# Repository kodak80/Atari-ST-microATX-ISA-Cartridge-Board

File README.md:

# Atari ST microATX ISA Cartridge Board

ISA board to allow the original Atari ST cartridge socket on a card. It brings
the ST cartridge port out to an ISA (16-bit) card outline and an internal
40-pin IDC header, so the cartridge bus can be used inside a microATX case
build. Board silkscreen: *Atari ST ATX Cartridge Port ISA Adapter v1.3 —
kodak80 (2022)*.

## Board

- Two-layer PCB in an ISA 16-bit card outline (`ST1`)
- Atari ST cartridge port connection (`U$1`) with ROM3/ROM4 select lines
- Internal 40-pin IDC header (`J1`) carrying the cartridge bus
- DIP-16 socket (`J2`) for a Dallas-style RTC ("FMC-II RTC"), with crystal
  (`Y1`) and CR1220 coin-cell holder (`BT1`)
- Jumper option on the board (`JP`)

## Files

| File | Contents |
|------|----------|
| `Cart Adapter RTC 40 pin Header SMD CR1220.kicad_pro` | KiCad project |
| `Cart Adapter RTC 40 pin Header SMD CR1220.kicad_sch` | Schematic |
| `Cart Adapter RTC 40 pin Header SMD CR1220.kicad_pcb` | PCB layout |
| `IDC-Header_2x20_P2.54mm_Vertical_kodak80.kicad_mod` | Custom 2×20 IDC header footprint |
| `empty.kicad_wks` | Drawing sheet |

Created in KiCad 6; opens in later versions (they will offer to upgrade the
file format on save). The schematic was originally imported from Eagle, so
several symbols live in the embedded `Cart Adapter-eagle-import` library.

## Revision

v1.3

## TheHulk ISA card (branch `thehulk-isa`)

[`thehulk-isa/`](thehulk-isa/) merges RetroLoft's [TheHulk](https://github.com/RetroLoft/thehulk)
network/SD storage cartridge onto this card: schematic done, PCB is this v1.3 board with the socket
and RTC removed and TheHulk's parts added, ready to be placed. KiCad 9, GPL-3.0. See
[`thehulk-isa/ROUTING.md`](thehulk-isa/ROUTING.md).

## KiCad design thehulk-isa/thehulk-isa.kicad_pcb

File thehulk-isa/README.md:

# TheHulk ISA card

[TheHulk](https://github.com/RetroLoft/thehulk) (RetroLoft's network and SD card storage cartridge for
the Atari ST, ESP32-S3 + iCE40UP5K) moved onto the Atari ST mATX ISA cartridge board in the parent
folder. The cartridge bus reaches the card through the ISA edge (same pinout as the v1.3 board) or
the internal 40-pin header J1. The /ROM3 and /ROM4 pads are kept for the flying wires from the
motherboard.

KiCad 9 project, based on TheHulk `hardware/prod-v2` (commit `c8f1c73`).

## What changed from TheHulk prod-v2

- **Cartridge edge removed.** The 40-pin cartridge connector `CON1` is now `J1`, a 2×20 IDC header
  (`isa_card:IDC-Header_2x20_P2.54mm_Vertical_kodak80`). Its pins are numbered exactly like the cartridge
  port, so nothing else in TheHulk's circuit changed.
- **ISA edge added** (`ST1`, `isa_card:ISA_16bit_Edge` / `isa_card:IBM16BIT`) on the same nets as
  v1.3: D0–D15, A1–A15, /UDS, /LDS, +5V, GND. The ISA pins v1.3 had but the cartridge port doesn't
  (A16–A19, RDY2, VRES, MEMRD/MEMWR, ±12V) are marked no-connect.
- **/ROM3 and /ROM4 wire pads** (`ROM3`, `ROM4`), as on v1.3.
- **FMC-II RTC socket and the passthrough cartridge socket are gone.**
- Everything else is TheHulk prod-v2 unchanged: same parts, same nets, same FPGA and ESP32 pins, so
  TheHulk's gateware and firmware should run as they are.

## PCB

Fresh start from the v1.3 board (`Cart Adapter RTC 40 pin Header SMD CR1220.kicad_pcb`):

- **Kept exactly as v1.3:** card outline, ISA edge (ST1), J1 and the /ROM3, /ROM4 pads in their
  v1.3 positions, and your v1.3 routing between the ISA edge, J1 and the /ROM pads.
- **Removed:** the cartridge socket, the FMC-II RTC (Dallas socket, crystal, CR1220 holder), their
  silkscreen labels, and the v1.3 tracks that only went to them.
- **Added, not placed:** all 74 of TheHulk's parts (everything except its cartridge edge), with
  their nets, sitting below the card in TheHulk's own arrangement under the label
  "TheHulk parts - to be placed". No tracks.
- Net class: TheHulk's (0.2 mm tracks, 0.6/0.3 mm vias) with the clearance set to 0.1524 mm (6 mil),
  the clearance your v1.3 routing was laid out to. TheHulk's own layout also meets it.

## License

GPL-3.0 (see `LICENSE`), as TheHulk. TheHulk is by RetroLoft; GEMDRIVE is based on the
SidecarTridge Multi-device project by Diego Parrilla Santamaría (GOODDATA LABS SL).

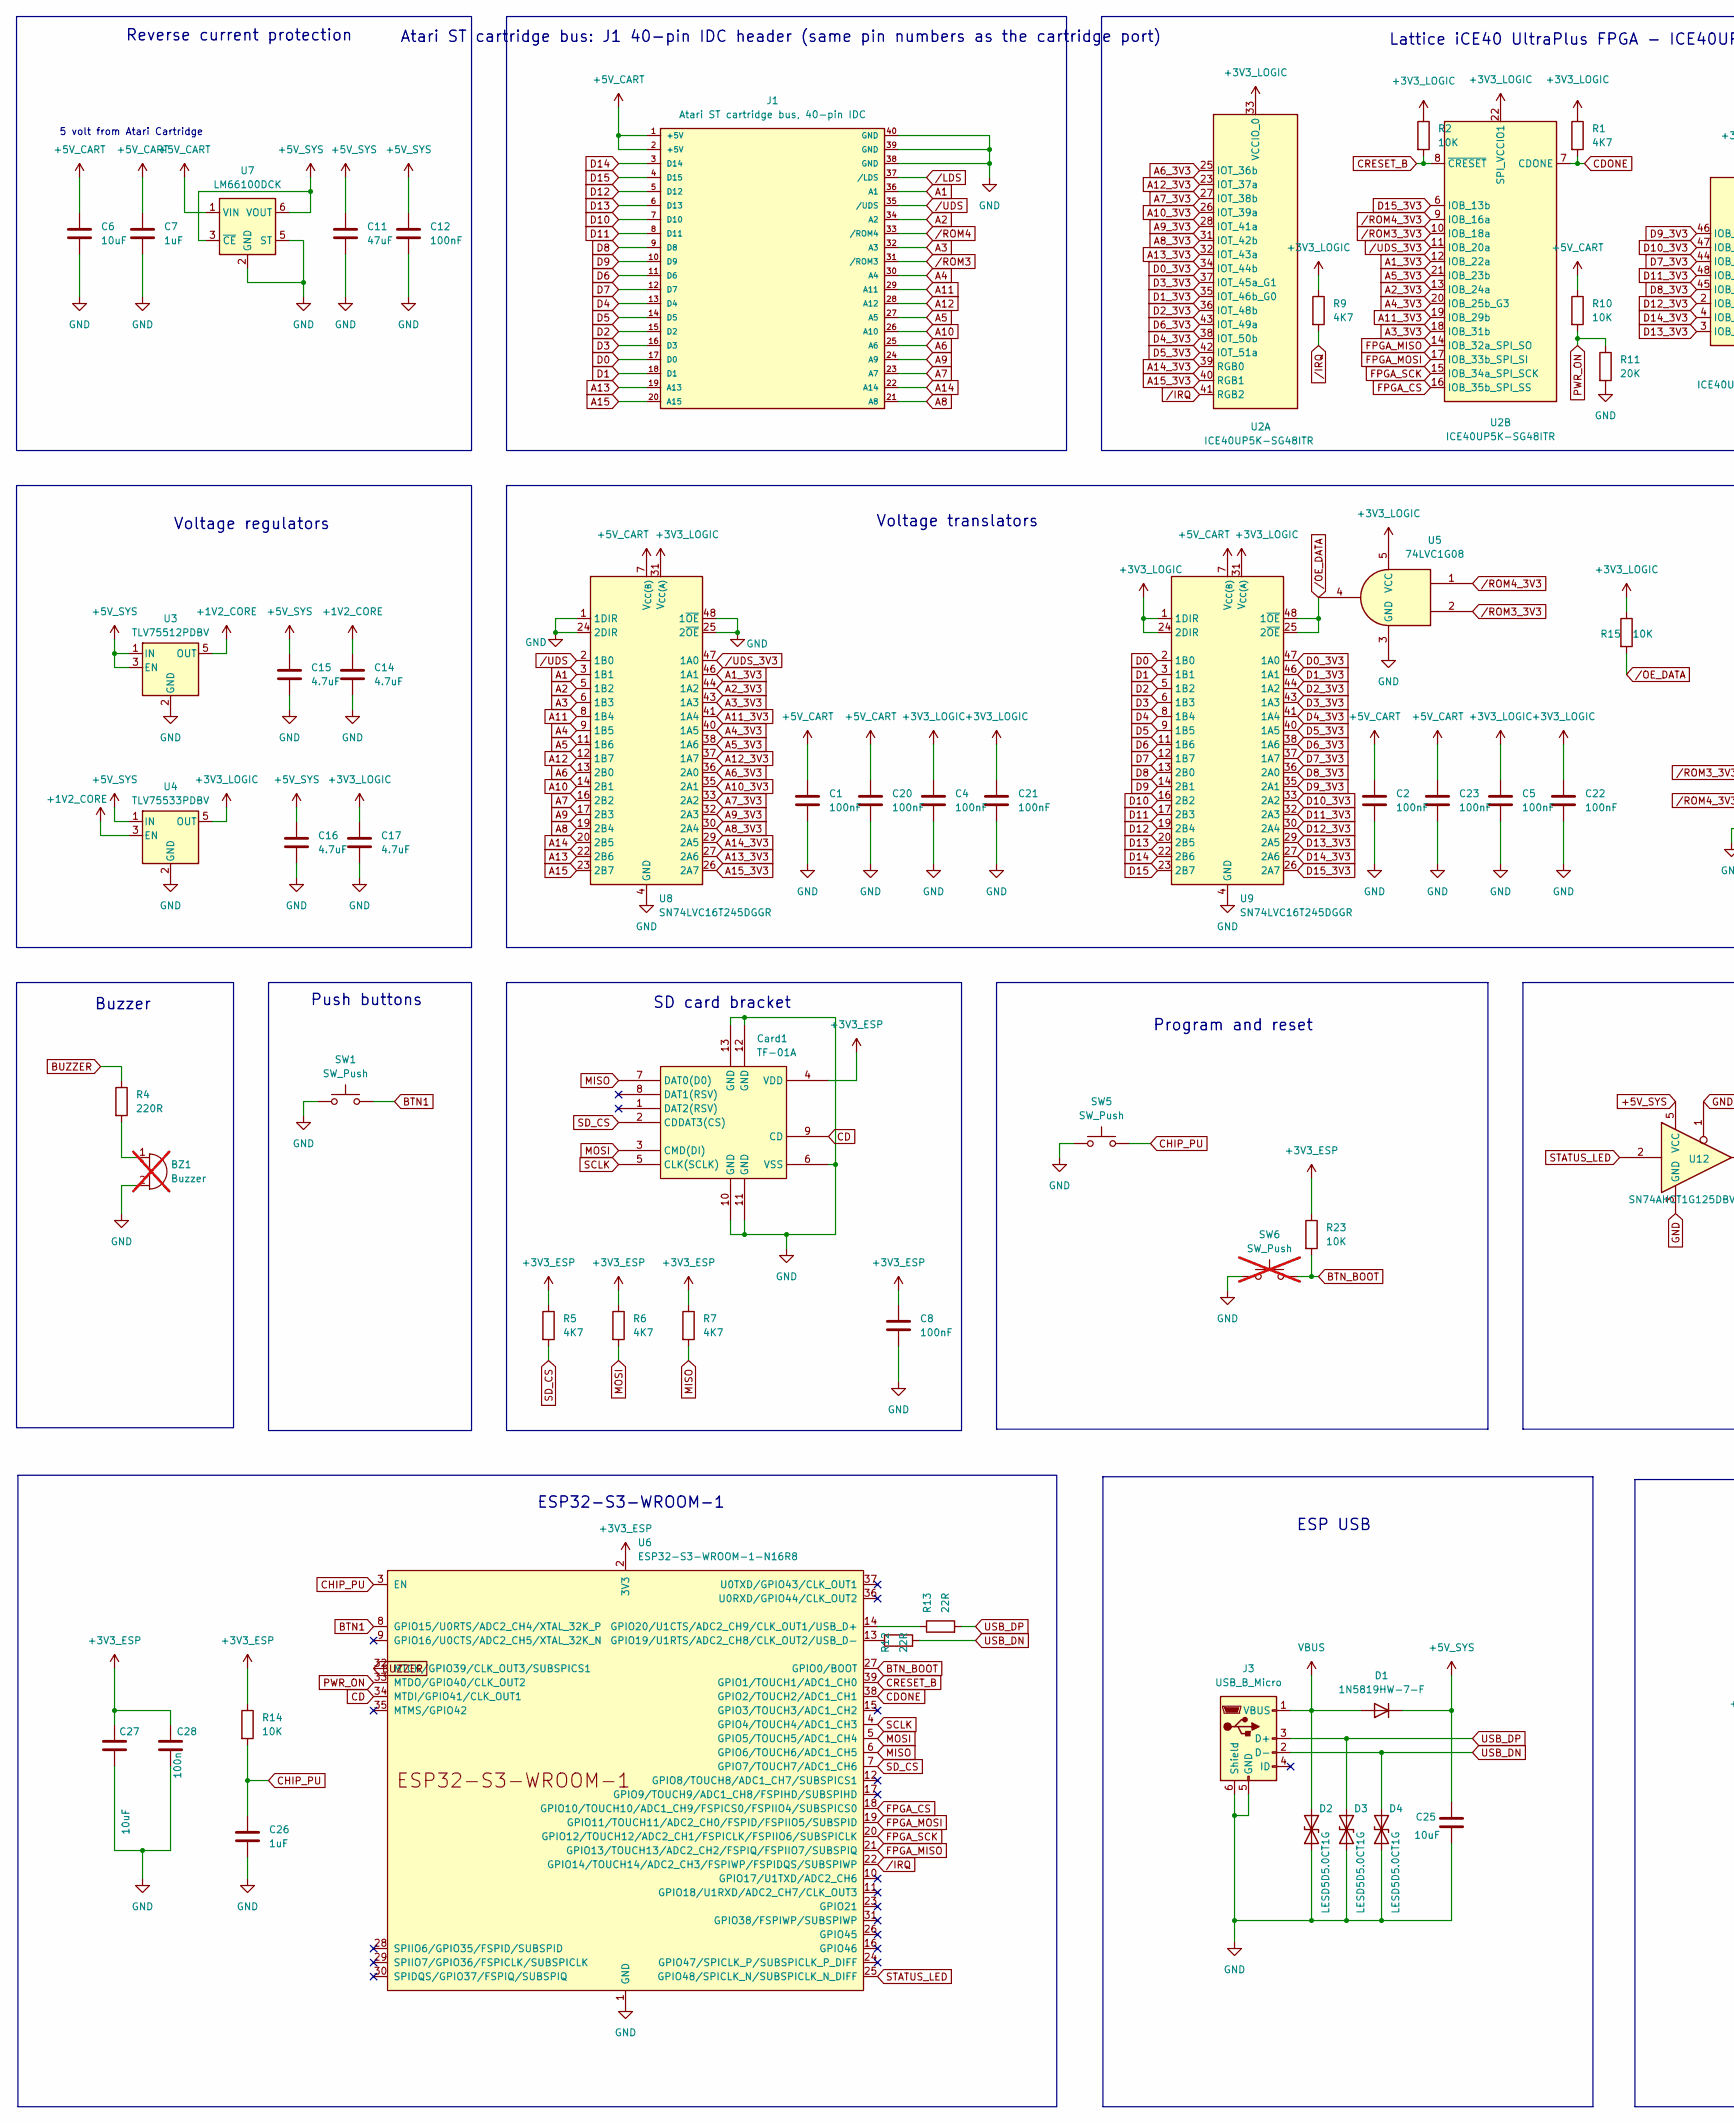
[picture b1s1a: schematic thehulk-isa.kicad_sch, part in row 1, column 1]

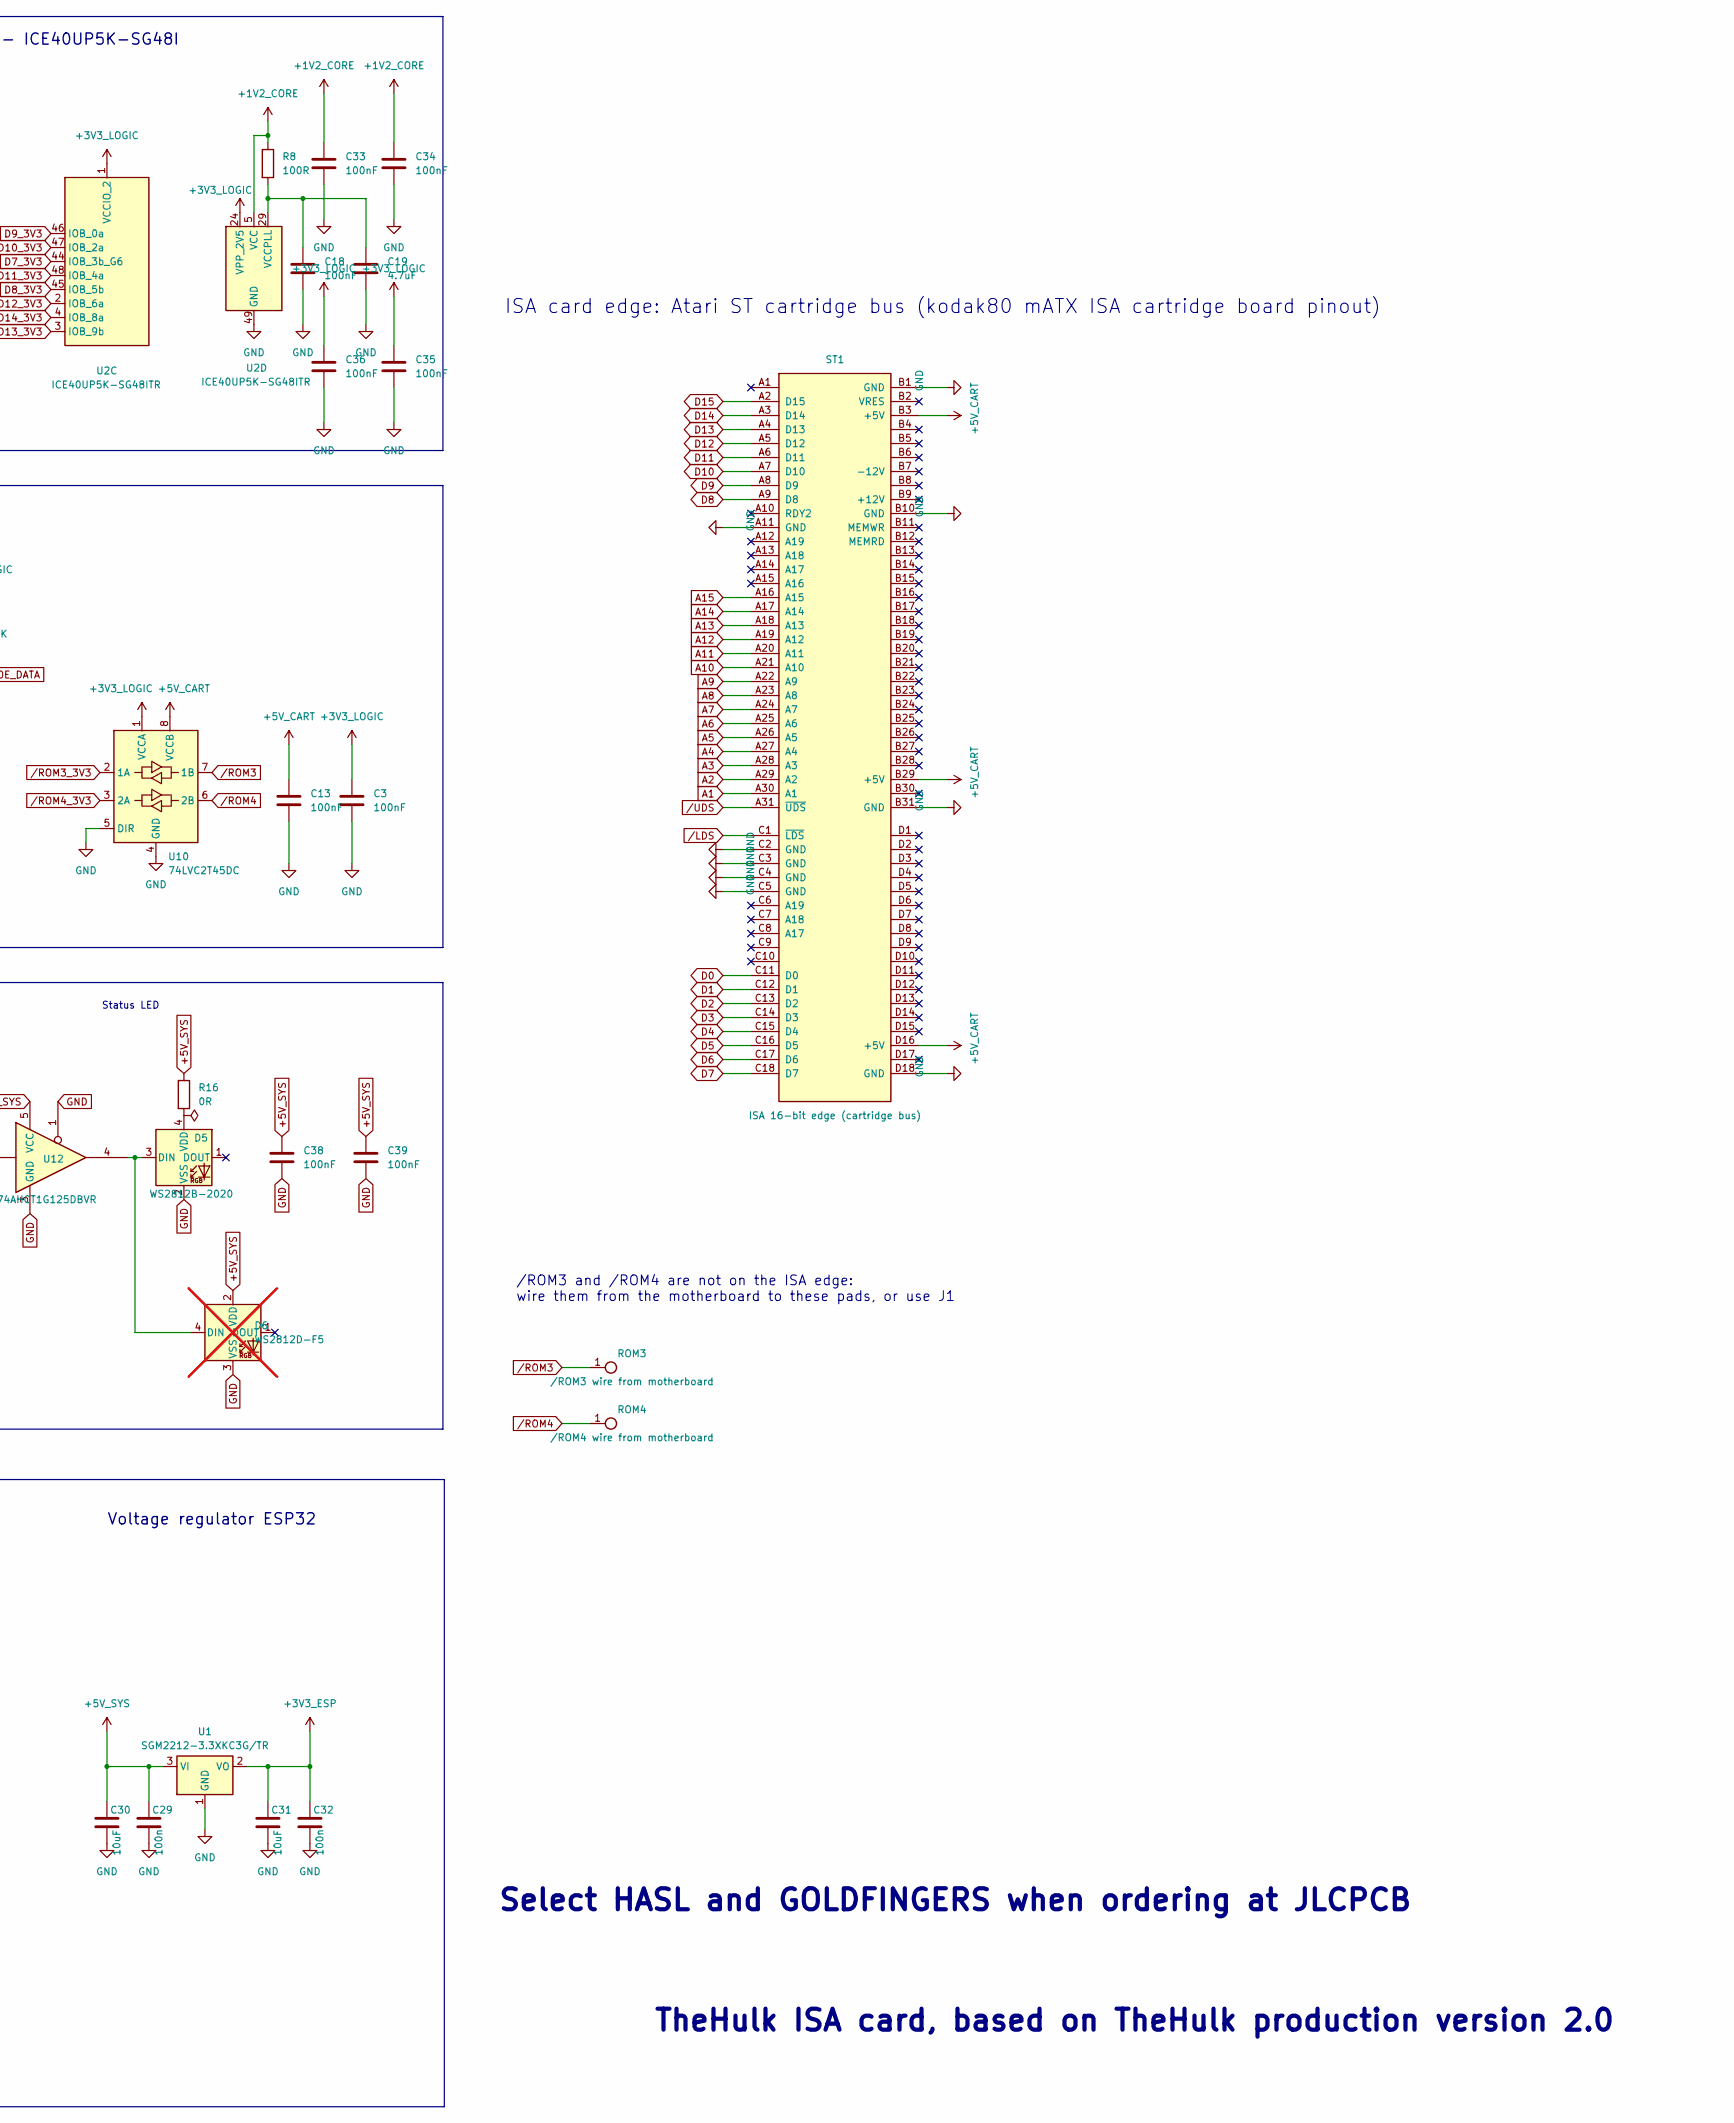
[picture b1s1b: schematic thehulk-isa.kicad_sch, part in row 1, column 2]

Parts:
BZ1: Buzzer; Buzzer_12x9.5RM7.6; not fitted
C1, C2, C3, C4, C5, C8, C12, C13, C18, C20, C21, C22, C23, C33, C34, C35, C36, C38, C39: 100nF; C_0402_1005Metric; LCSC Part C1525
C6, C25, C27, C30, C31: 10uF; C_0603_1608Metric; LCSC Part C19702
C7: 1uF; C_0402_1005Metric; LCSC Part C52923
C11: 47uF; C_0805_2012Metric; LCSC Part C16780
C14, C15, C16, C17, C19: 4.7uF; C_0603_1608Metric; LCSC Part C19666
C26: 1uF; C_0603_1608Metric; LCSC Part C15849
C28, C29, C32: 100n; C_0603_1608Metric; LCSC Part C14663
Card1: TF-01A; TF-SMD_TF-01A; MPN TF-01A; LCSC Part C91145
D1: 1N5819HW-7-F; D_SOD-123; LCSC Part C82544
D2, D3, D4: LESD5D5.0CT1G; D_SOD-523; LCSC Part C5199850
D5: WS2812B-2020; LED_WS2812B-2020_PLCC4_2.0x2.0mm; LCSC Part C52917434
D6: WS2812D-F5; LED_D5.0mm-4_WS2812D-F5; LCSC Part C190565; not fitted
J1: Atari ST cartridge bus, 40-pin IDC; IDC-Header_2x20_P2.54mm_Vertical_kodak80
J3: USB_B_Micro; USB_Micro-B_C10418; MPN Jing Extension 920-E52A2021S10100; LCSC Part C10418
R1, R5, R6, R7, R9: 4K7; R_0402_1005Metric; LCSC Part C25900
R2, R10: 10K; R_0402_1005Metric; LCSC Part C25744
R4: 220R; R_0603_1608Metric; LCSC Part C22962
R8: 100R; R_0402_1005Metric; LCSC Part C25076
R11: 20K; R_0402_1005Metric; LCSC Part C25765
R12, R13: 22R; R_0402_1005Metric; LCSC Part C25092
R14, R15, R23: 10K; R_0603_1608Metric; LCSC Part C25804
R16: 0R; R_0805_2012Metric; LCSC Part C17477
ROM3: /ROM3 wire from motherboard; 1X01
ROM4: /ROM4 wire from motherboard; 1X01
ST1: ISA 16-bit edge (cartridge bus); IBM16BIT
SW1: SW_Push; SW_Tactile_6x6_SMD_H9.5; MPN Kinghelm KH-6X6X9.5H-SMT (9.5 mm); LCSC Part C3038675
SW5: SW_Push; SW_SPST_B3U-1000P; LCSC Part C231329
SW6: SW_Push; SW_SPST_B3U-1000P; LCSC Part C231329; not fitted
U1: SGM2212-3.3XKC3G/TR; SOT-223-3_TabPin2; LCSC Part C3294699
U2: ICE40UP5K-SG48ITR; QFN-48-1EP_7x7mm_P0.5mm_EP5.6x5.6mm; LCSC Part C2678152
U3: TLV75512PDBV; SOT-23-5; LCSC Part C2877864
U4: TLV75533PDBV; SOT-23-5; LCSC Part C404027
U5: 74LVC1G08; SOT-23-5; LCSC Part C7666
U6: ESP32-S3-WROOM-1-N16R8; ESP32-S3-WROOM-1; LCSC Part C2913202
U7: LM66100DCK; SOT-363_SC-70-6; LCSC Part C2869734
U8, U9: SN74LVC16T245DGGR; TSSOP-48_6.1x12.5mm_P0.5mm; LCSC C148170
U10: 74LVC2T45DC; VSSOP-8_2.3x2mm_P0.5mm; LCSC Part C15741
U12: SN74AHCT1G125DBVR; SOT-23-5; LCSC Part C7484

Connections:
+1V2_CORE: C14.1, C33.1, C34.1, R8.1, U2.5 (VCC), U2.30 (VCC), U3.5 (OUT), U4.3 (EN)
+3V3_ESP: C8.1, C27.1, C28.1, C31.1, C32.1, Card1.4 (VDD), R5.1, R6.1, R7.1, R14.1, R23.1, U1.2 (VO), U6.2 (3V3)
+3V3_LOGIC: C3.1, C4.1, C5.1, C17.1, C21.1, C22.1, C35.1, C36.1, R1.1, R2.1, R9.1, R15.1, U2.1 (VCCIO_2), U2.22 (SPI_VCCIO1), U2.24 (VPP_2V5), U2.33 (VCCIO_0), U4.5 (OUT), U5.5 (VCC), U8.31 (V_{CC(A)}), U8.42 (V_{CC(A)}), U9.1 (1DIR), U9.24 (2DIR), U9.31 (V_{CC(A)}), U9.42 (V_{CC(A)}), U10.1 (VCCA)
+5V_CART: C1.1, C2.1, C6.1, C7.1, C13.1, C20.1, C23.1, J1.1, J1.2, R10.1, ST1.B3, ST1.B29, ST1.D16, U7.1 (VIN), U8.7 (V_{CC(B)}), U8.18 (V_{CC(B)}), U9.7 (V_{CC(B)}), U9.18 (V_{CC(B)}), U10.8 (VCCB)
+5V_SYS: C11.1, C12.1, C15.1, C16.1, C25.1, C29.1, C30.1, C38.1, C39.1, D1.1 (K), D6.2 (VDD), R16.1, U1.3 (VI), U3.1 (IN), U3.3 (EN), U4.1 (IN), U7.3 (~CE), U7.6 (VOUT), U12.5 (VCC)
A1: J1.36, ST1.A30, U8.3 (1B1)
A1_3V3: U2.12 (IOB_22a), U8.46 (1A1)
A2: J1.34, ST1.A29, U8.5 (1B2)
A2_3V3: U2.13 (IOB_24a), U8.44 (1A2)
A3: J1.32, ST1.A28, U8.6 (1B3)
A3_3V3: U2.18 (IOB_31b), U8.43 (1A3)
A4: J1.30, ST1.A27, U8.9 (1B5)
A4_3V3: U2.20 (IOB_25b_G3), U8.40 (1A5)
A5: J1.27, ST1.A26, U8.11 (1B6)
A5_3V3: U2.21 (IOB_23b), U8.38 (1A6)
A6: J1.25, ST1.A25, U8.13 (2B0)
A6_3V3: U2.25 (IOT_36b), U8.36 (2A0)
A7: J1.23, ST1.A24, U8.16 (2B2)
A7_3V3: U2.27 (IOT_38b), U8.33 (2A2)
A8: J1.21, ST1.A23, U8.19 (2B4)
A8_3V3: U2.31 (IOT_42b), U8.30 (2A4)
A9: J1.24, ST1.A22, U8.17 (2B3)
A9_3V3: U2.28 (IOT_41a), U8.32 (2A3)
A10: J1.26, ST1.A21, U8.14 (2B1)
A10_3V3: U2.26 (IOT_39a), U8.35 (2A1)
A11: J1.29, ST1.A20, U8.8 (1B4)
A11_3V3: U2.19 (IOB_29b), U8.41 (1A4)
A12: J1.28, ST1.A19, U8.12 (1B7)
A12_3V3: U2.23 (IOT_37a), U8.37 (1A7)
A13: J1.19, ST1.A18, U8.22 (2B6)
A13_3V3: U2.32 (IOT_43a), U8.27 (2A6)
A14: J1.22, ST1.A17, U8.20 (2B5)
A14_3V3: U2.39 (RGB0), U8.29 (2A5)
A15: J1.20, ST1.A16, U8.23 (2B7)
A15_3V3: U2.40 (RGB1), U8.26 (2A7)
BTN1: SW1.2, U6.8 (GPIO15/U0RTS/ADC2_CH4/XTAL_32K_P)
BTN_BOOT: R23.2, SW6.2, U6.27 (GPIO0/BOOT)
BUZZER: R4.1, U6.32 (MTCK/GPIO39/CLK_OUT3/SUBSPICS1)
CD: Card1.9 (CD), U6.34 (MTDI/GPIO41/CLK_OUT1)
CDONE: R1.2, U2.7 (CDONE), U6.38 (GPIO2/TOUCH2/ADC1_CH1)
CHIP_PU: C26.1, R14.2, SW5.2, U6.3 (EN)
CRESET_B: R2.2, U2.8 (~CRESET), U6.39 (GPIO1/TOUCH1/ADC1_CH0)
D0: J1.17, ST1.C11, U9.2 (1B0)
D0_3V3: U2.34 (IOT_44b), U9.47 (1A0)
D1: J1.18, ST1.C12, U9.3 (1B1)
D1_3V3: U2.35 (IOT_46b_G0), U9.46 (1A1)
D2: J1.15, ST1.C13, U9.5 (1B2)
D2_3V3: U2.36 (IOT_48b), U9.44 (1A2)
D3: J1.16, ST1.C14, U9.6 (1B3)
D3_3V3: U2.37 (IOT_45a_G1), U9.43 (1A3)
D4: J1.13, ST1.C15, U9.8 (1B4)
D4_3V3: U2.38 (IOT_50b), U9.41 (1A4)
D5: J1.14, ST1.C16, U9.9 (1B5)
D5_3V3: U2.42 (IOT_51a), U9.40 (1A5)
D6: J1.11, ST1.C17, U9.11 (1B6)
D6_3V3: U2.43 (IOT_49a), U9.38 (1A6)
D7: J1.12, ST1.C18, U9.12 (1B7)
D7_3V3: U2.44 (IOB_3b_G6), U9.37 (1A7)
D8: J1.9, ST1.A9, U9.13 (2B0)
D8_3V3: U2.45 (IOB_5b), U9.36 (2A0)
D9: J1.10, ST1.A8, U9.14 (2B1)
D9_3V3: U2.46 (IOB_0a), U9.35 (2A1)
D10: J1.7, ST1.A7, U9.16 (2B2)
D10_3V3: U2.47 (IOB_2a), U9.33 (2A2)
D11: J1.8, ST1.A6, U9.17 (2B3)
D11_3V3: U2.48 (IOB_4a), U9.32 (2A3)
D12: J1.5, ST1.A5, U9.19 (2B4)
D12_3V3: U2.2 (IOB_6a), U9.30 (2A4)
D13: J1.6, ST1.A4, U9.20 (2B5)
D13_3V3: U2.3 (IOB_9b), U9.29 (2A5)
D14: J1.3, ST1.A3, U9.22 (2B6)
D14_3V3: U2.4 (IOB_8a), U9.27 (2A6)
D15: J1.4, ST1.A2, U9.23 (2B7)
D15_3V3: U2.6 (IOB_13b), U9.26 (2A7)
FPGA_CS: U2.16 (IOB_35b_SPI_SS), U6.18 (GPIO10/TOUCH10/ADC1_CH9/FSPICS0/FSPIIO4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)
FPGA_MISO: U2.14 (IOB_32a_SPI_SO), U6.21 (GPIO13/TOUCH13/ADC2_CH2/FSPIQ/FSPIIO7/S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)
FPGA_MOSI: U2.17 (IOB_33b_SPI_SI), U6.19 (GPIO11/TOUCH11/ADC2_CH0/FSPID/FSPIIO5/S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)
FPGA_SCK: U2.15 (IOB_34a_SPI_SCK), U6.20 (GPIO12/TOUCH12/ADC2_CH1/FSPICLK/FSPIIO6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)
GND: BZ1.2 (-), C1.2, C2.2, C3.2, C4.2, C5.2, C6.2, C7.2, C8.2, C11.2, C12.2, C13.2, C14.2, C15.2, C16.2, C17.2, C18.2, C19.2, C20.2, C21.2, C22.2, C23.2, C25.2, C26.2, C27.2, C28.2, C29.2, C30.2, C31.2, C32.2, C33.2, C34.2, C35.2, C36.2, C38.2, C39.2, Card1.6 (VSS), Card1.10 (GND), Card1.11 (GND), Card1.12 (GND), Card1.13 (GND), D2.1 (A1), D3.1 (A1), D4.1 (A1), D5.2 (VSS), D6.3 (VSS), J1.38, J1.39, J1.40, J3.5 (GND), J3.6 (Shield), R11.2, ST1.A11, ST1.B1, ST1.B10, ST1.B31, ST1.C2, ST1.C3, ST1.C4, ST1.C5, ST1.D18, SW1.1, SW5.1, SW6.1, U1.1 (GND), U2.49 (GND), U3.2 (GND), U4.2 (GND), U5.3 (GND), U6.1 (GND), U6.40 (GND), U6.41 (GND), U7.2 (GND), U7.5 (ST), U8.1 (1DIR), U8.4 (GND), U8.10 (GND), U8.15 (GND), U8.21 (GND), U8.24 (2DIR), U8.25 (2~OE), U8.28 (GND), U8.34 (GND), U8.39 (GND), U8.45 (GND), U8.48 (1~OE), U9.4 (GND), U9.10 (GND), U9.15 (GND), U9.21 (GND), U9.28 (GND), U9.34 (GND), U9.39 (GND), U9.45 (GND), U10.4 (GND), U10.5 (DIR), U12.1, U12.3 (GND)
MISO: Card1.7 (DAT0(D0)), R7.2, U6.6 (GPIO6/TOUCH6/ADC1_CH5)
MOSI: Card1.3 (CMD(DI)), R6.2, U6.5 (GPIO5/TOUCH5/ADC1_CH4)
unnamed: BZ1.1 (+), R4.2
unnamed: D5.3 (DIN), D6.4 (DIN), U12.4
unnamed: D5.4 (VDD), R16.2
unnamed: C18.1, C19.1, R8.2, U2.29 (VCCPLL)
unnamed: R12.1, U6.13 (GPIO19/U1RTS/ADC2_CH8/CLK_OUT2/USB_D-)
unnamed: R13.1, U6.14 (GPIO20/U1CTS/ADC2_CH9/CLK_OUT1/USB_D+)
PWR_ON: R10.2, R11.1, U6.33 (MTDO/GPIO40/CLK_OUT2)
SCLK: Card1.5 (CLK(SCLK)), U6.4 (GPIO4/TOUCH4/ADC1_CH3)
SD_CS: Card1.2 (CDDAT3(CS)), R5.2, U6.7 (GPIO7/TOUCH7/ADC1_CH6)
STATUS_LED: U6.25 (GPIO48/SPICLK_N/SUBSPICLK_N_DIFF), U12.2
USB_DN: D4.2 (A2), J3.2 (D-), R12.2
USB_DP: D3.2 (A2), J3.3 (D+), R13.2
VBUS: D1.2 (A), D2.2 (A2), J3.1 (VBUS)
/IRQ: R9.2, U2.41 (RGB2), U6.22 (GPIO14/TOUCH14/ADC2_CH3/FSPIWP/FSPIDQS/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)
/LDS: J1.37, ST1.C1
/OE_DATA: R15.2, U5.4, U9.25 (2~OE), U9.48 (1~OE)
/ROM3: J1.31, ROM3.1, U10.7 (1B)
/ROM3_3V3: U2.10 (IOB_18a), U5.2, U10.2 (1A)
/ROM4: J1.33, ROM4.1, U10.6 (2B)
/ROM4_3V3: U2.9 (IOB_16a), U5.1, U10.3 (2A)
/UDS: J1.35, ST1.A31, U8.2 (1B0)
/UDS_3V3: U2.11 (IOB_20a), U8.47 (1A0)

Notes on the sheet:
Select HASL and GOLDFINGERS when ordering at JLCPCB
5 volt from Atari Cartridge
Buzzer
Reverse current protection
ESP USB
TheHulk ISA card, based on TheHulk production version 2.0
SD card bracket
Program and reset
Voltage regulators
Push buttons
Lattice iCE40 UltraPlus FPGA - ICE40UP5K-SG48I
Voltage translators
ESP32-S3-WROOM-1
Voltage regulator ESP32
Atari ST cartridge bus: J1 40-pin IDC header (same pin numbers as the cartridge port)
Status LED
ISA card edge: Atari ST cartridge bus (kodak80 mATX ISA cartridge board pinout)
/ROM3 and /ROM4 are not on the ISA edge: wire them from the motherboard to these pads, or use J1

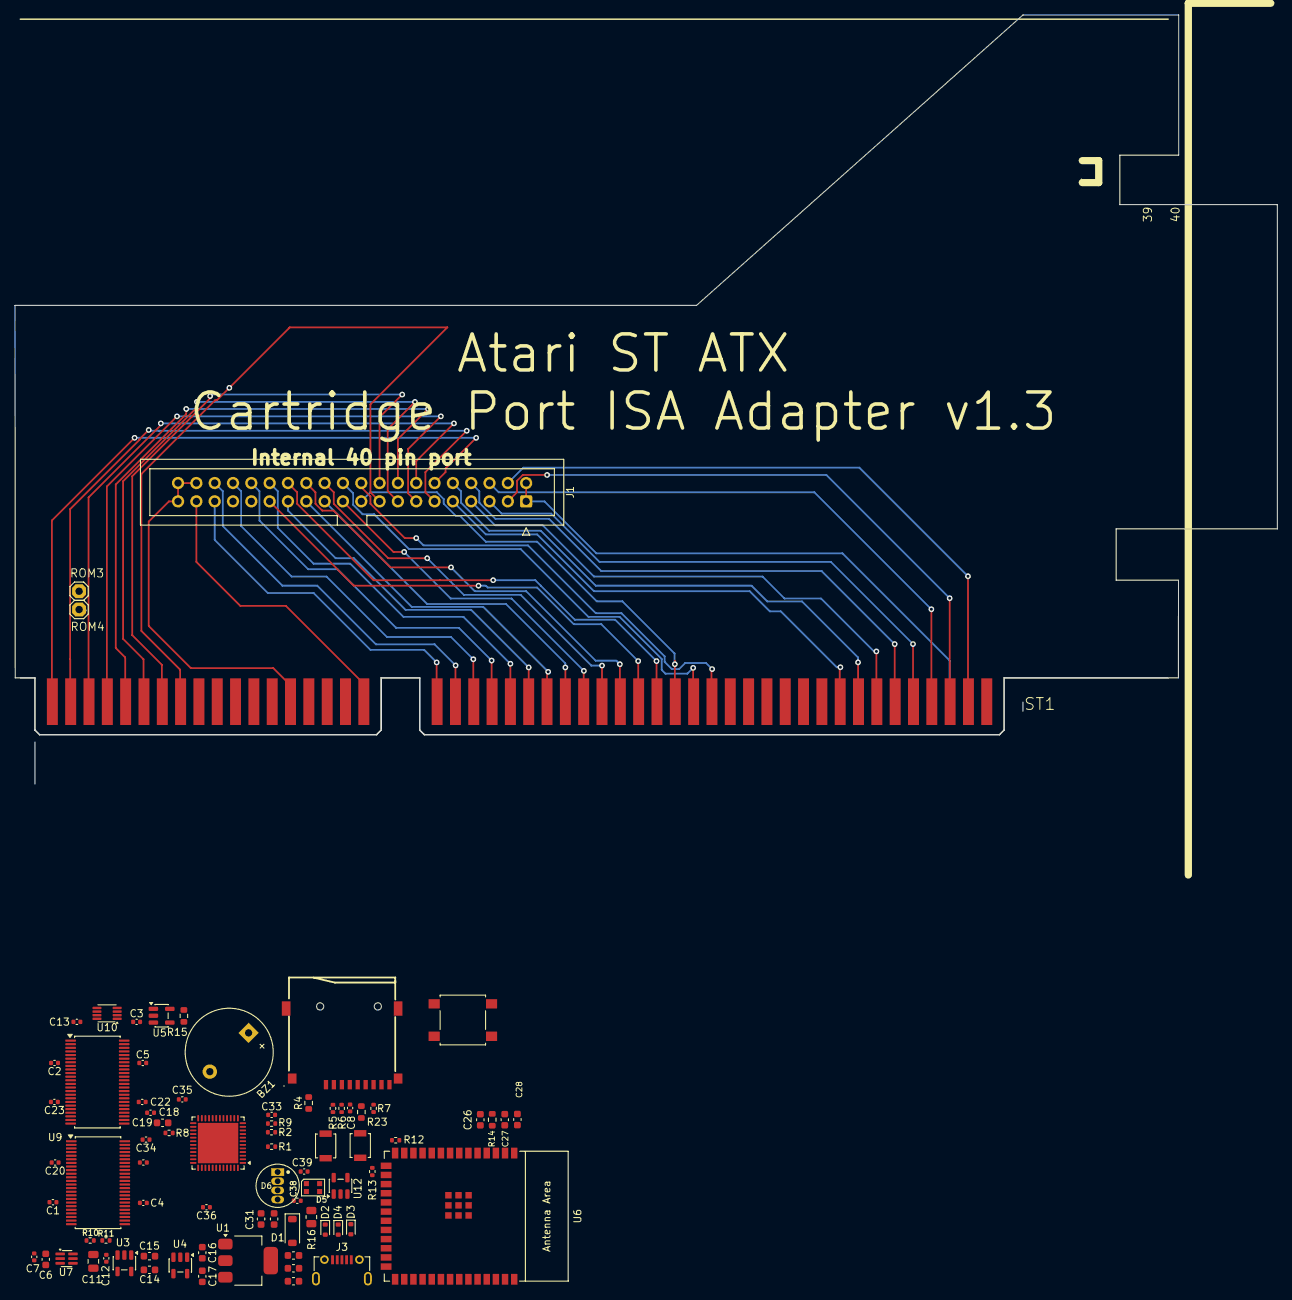
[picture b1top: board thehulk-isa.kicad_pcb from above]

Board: 2 copper layers, 175.0 x 106.6 mm, 78 parts (0 on the bottom side), 103 nets.

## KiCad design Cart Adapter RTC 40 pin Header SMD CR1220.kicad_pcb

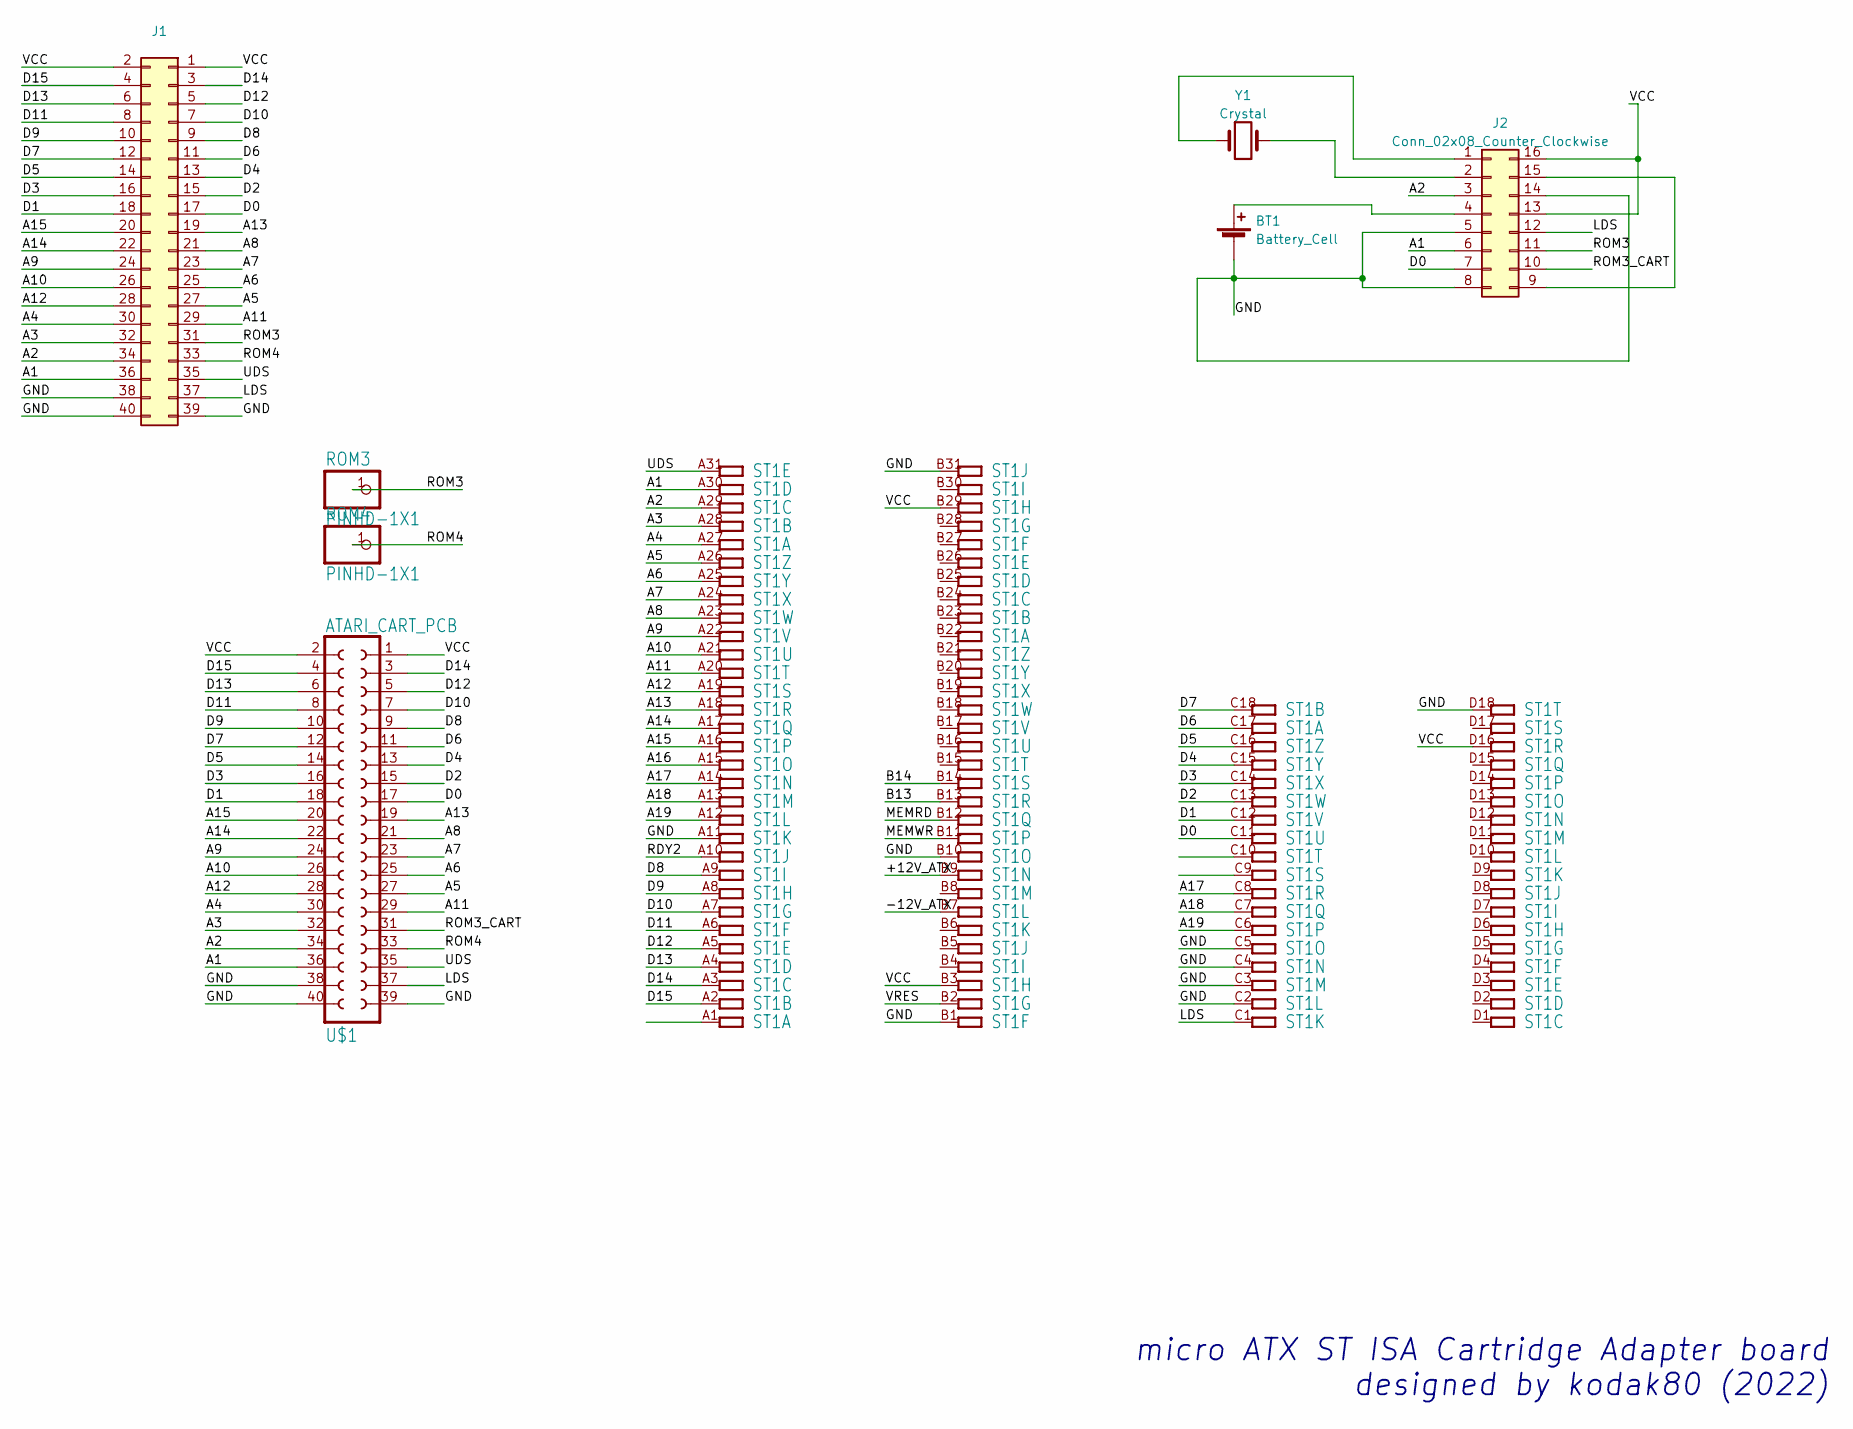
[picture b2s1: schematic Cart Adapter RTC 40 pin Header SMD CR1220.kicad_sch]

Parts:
BT1: Battery_Cell
J1: (no value)
J2: Conn_02x08_Counter_Clockwise; DIP-16_W7.62mm_Socket_LongPads
ROM3, ROM4: PINHD-1X1; 1X01
ST1: IBM16BIT
U$1: ATARI_CART_PCB; 40_PIN_HEADER
Y1: Crystal; Crystal_AT310_D3.0mm_L10.0mm_Horizontal

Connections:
/+12V_ATX: ST1.B9
/-12V_ATX: ST1.B7
/A1: J1.36, J2.6, ST1.A30, U$1.36
/A2: J1.34, J2.3, ST1.A29, U$1.34
/A3: J1.32, ST1.A28, U$1.32
/A4: J1.30, ST1.A27, U$1.30
/A5: J1.27, ST1.A26, U$1.27
/A6: J1.25, ST1.A25, U$1.25
/A7: J1.23, ST1.A24, U$1.23
/A8: J1.21, ST1.A23, U$1.21
/A9: J1.24, ST1.A22, U$1.24
/A10: J1.26, ST1.A21, U$1.26
/A11: J1.29, ST1.A20, U$1.29
/A12: J1.28, ST1.A19, U$1.28
/A13: J1.19, ST1.A18, U$1.19
/A14: J1.22, ST1.A17, U$1.22
/A15: J1.20, ST1.A16, U$1.20
/A16: ST1.A15
/A17: ST1.A14, ST1.C8
/A18: ST1.A13, ST1.C7
/A19: ST1.A12, ST1.C6
/B13: ST1.B13
/B14: ST1.B14
/D0: J1.17, J2.7, ST1.C11, U$1.17
/D1: J1.18, ST1.C12, U$1.18
/D2: J1.15, ST1.C13, U$1.15
/D3: J1.16, ST1.C14, U$1.16
/D4: J1.13, ST1.C15, U$1.13
/D5: J1.14, ST1.C16, U$1.14
/D6: J1.11, ST1.C17, U$1.11
/D7: J1.12, ST1.C18, U$1.12
/D8: J1.9, ST1.A9, U$1.9
/D9: J1.10, ST1.A8, U$1.10
/D10: J1.7, ST1.A7, U$1.7
/D11: J1.8, ST1.A6, U$1.8
/D12: J1.5, ST1.A5, U$1.5
/D13: J1.6, ST1.A4, U$1.6
/D14: J1.3, ST1.A3, U$1.3
/D15: J1.4, ST1.A2, U$1.4
/GND: BT1.2 (-), J1.38, J1.39, J1.40, J2.5, J2.8, J2.14, ST1.A11, ST1.B1, ST1.B10, ST1.B31, ST1.C2, ST1.C3, ST1.C4, ST1.C5, ST1.D18, U$1.38, U$1.39, U$1.40
/LDS: J1.37, J2.12, ST1.C1, U$1.37
/MEMRD: ST1.B12
/MEMWR: ST1.B11
/RDY2: ST1.A10
/ROM3: J1.31, J2.11, ROM3.1
/ROM3_CART: J2.10, U$1.31
/ROM4: J1.33, ROM4.1, U$1.33
/UDS: J1.35, ST1.A31, U$1.35
/VCC: J1.1, J1.2, J2.13, J2.16, ST1.B3, ST1.B29, ST1.D16, U$1.1, U$1.2
/VRES: ST1.B2
unnamed: BT1.1 (+), J2.4
unnamed: J2.1, Y1.1
unnamed: J2.2, Y1.2
unnamed: J2.9, J2.15

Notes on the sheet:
micro ATX ST ISA Cartridge Adapter board designed by kodak80 (2022)

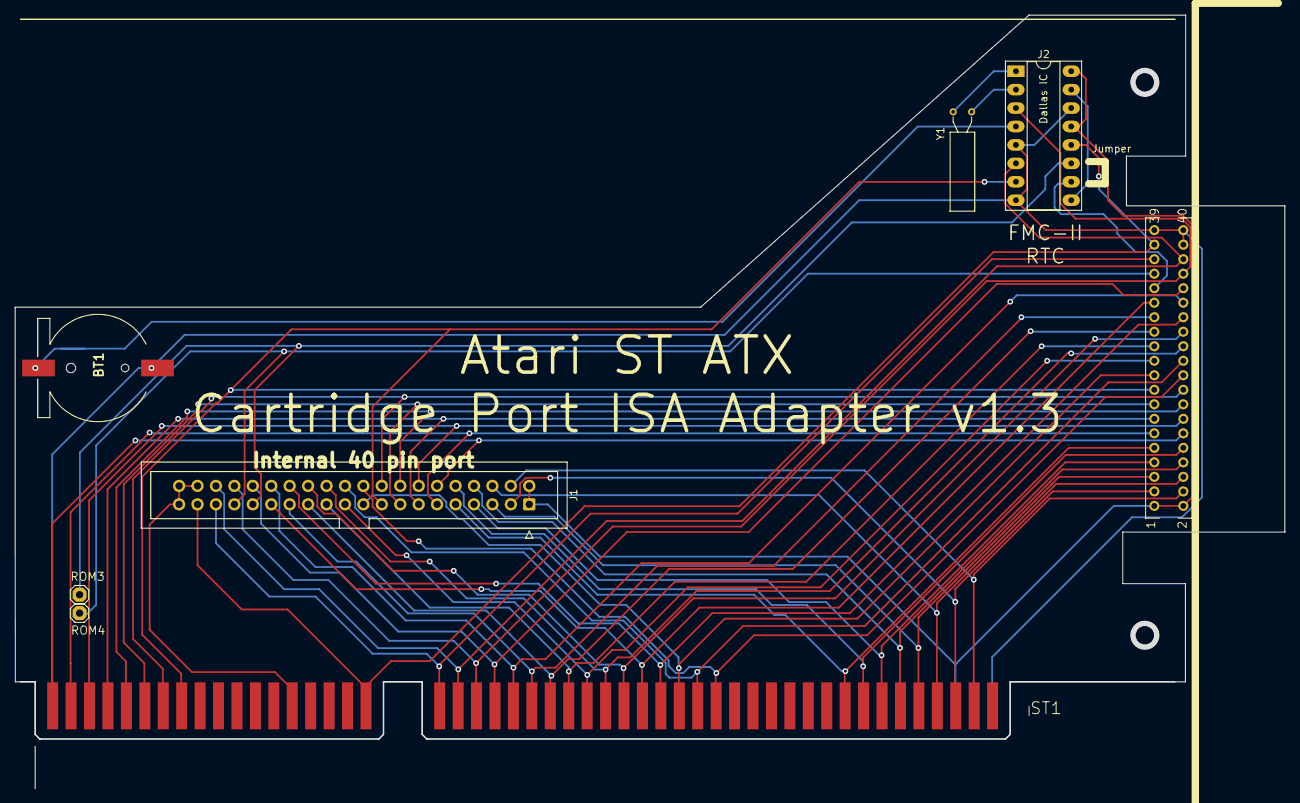
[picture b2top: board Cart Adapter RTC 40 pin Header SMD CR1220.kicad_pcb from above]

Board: 2 copper layers, 175.0 x 106.6 mm, 8 parts (0 on the bottom side), 45 nets.
